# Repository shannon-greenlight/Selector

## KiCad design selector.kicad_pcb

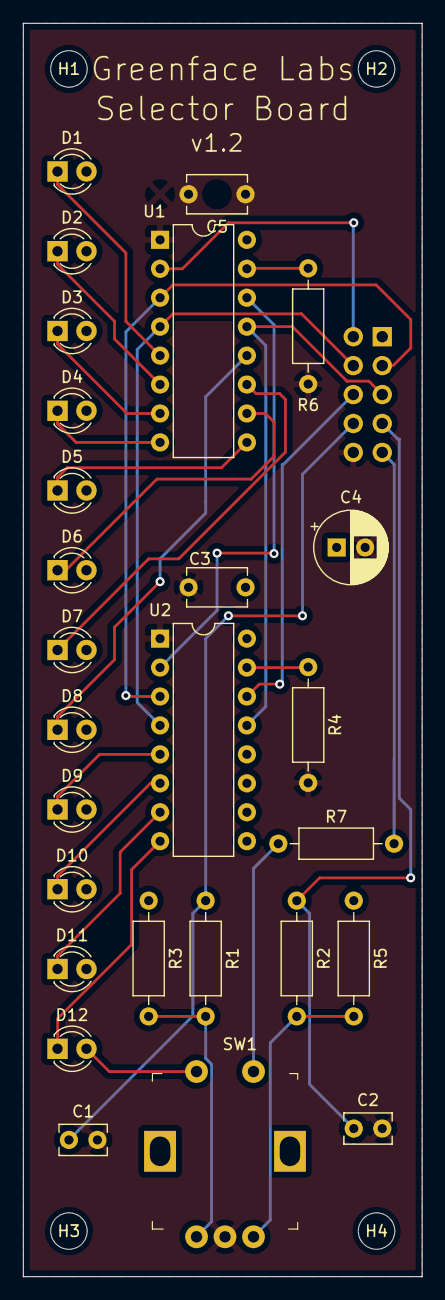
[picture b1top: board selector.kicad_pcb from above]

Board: 2 copper layers, 35.0 x 110.0 mm, 32 parts (1 on the bottom side), 28 nets.

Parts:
C1, C2: .01uF; C_Rect_L4.0mm_W2.5mm_P2.50mm
C3, C5: .1uF; C_Disc_D5.1mm_W3.2mm_P5.00mm
C4: 47uF; CP_Radial_D6.3mm_P2.50mm
D1, D2, D3, D4, D5, D6, D7, D8, D9, D10, D11, D12: Red LED; LED_D3.0mm
H1, H2, H3, H4: MountingHole; MountingHole_3.2mm_M3
J1: Conn_02x05_Odd_Even; PinHeader_2x05_P2.54mm_Vertical
R1, R2, R3, R5: 10K; R_Axial_DIN0207_L6.3mm_D2.5mm_P10.16mm_Horizontal
R4, R6: 2.2K; R_Axial_DIN0207_L6.3mm_D2.5mm_P10.16mm_Horizontal
R7: 1K; R_Axial_DIN0207_L6.3mm_D2.5mm_P10.16mm_Horizontal
SW1: PEC11R; Rotary_Encoder_Switched_PEC11R
U1, U2: TLC5916; DIP-16_W7.62mm

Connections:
+5V: C3.1, C4.1, C5.1, D1.2, D2.2, D3.2, D4.2, D5.2, D6.2, D7.2, D8.2, D9.2, D10.2, D11.2, D12.2, J1.1, R3.1, R5.1, SW1.1, U1.16, U2.16
GND: C1.2, C2.2, C3.2, C4.2, C5.2, J1.10, R4.2, R6.2, SW1.C, U1.1, U2.1
unnamed: C1.1, J1.8, R1.1
unnamed: C2.1, J1.7, R2.1
unnamed: D1.1, U1.5
unnamed: D2.1, U1.6
unnamed: D3.1, U1.7
unnamed: D4.1, U1.8
unnamed: D5.1, U1.9
unnamed: D6.1, U1.10
unnamed: D7.1, U1.11
unnamed: D8.1, U1.12
unnamed: D9.1, U2.5
unnamed: D10.1, U2.6
unnamed: D11.1, U2.7
unnamed: D12.1, U2.8
unnamed: J1.2, U1.2
unnamed: J1.3, U1.3, U2.3
unnamed: J1.4, U1.4, U2.4
unnamed: J1.5, U1.13, U2.13
unnamed: J1.6, U2.14
unnamed: J1.9, R7.2
unnamed: R1.2, R3.2, SW1.A
unnamed: R2.2, R5.2, SW1.B
unnamed: R4.1, U2.15
unnamed: R6.1, U1.15
unnamed: R7.1, SW1.2
unnamed: U1.14, U2.2

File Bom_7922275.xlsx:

Manufacturer Part Number | Manufacturer | Digi-Key Part Number | Customer Reference | Reference Designator | Packaging | Part Status | Quantity | Unit Price | Extended Price | Quantity Available | Mfg Std Lead Time | Description | RoHS Status | Lead Free Status | REACH Status
K103M15X7RF53L2 | Vishay BC Components | BC5136-ND | .01uF | C1 C2 | Bulk | Active | 2 | 0.21000 | $0.42 | 16243 | 10 Weeks | CAP CER 10000PF 50V X7R RADIAL | Not Available | Lead free | Not Available
ECE-A1EKA470I | Panasonic Electronic Components | P19582CT-ND | 47uF | C4 | Cut Tape (CT) | Active | 1 | 0.27000 | $0.27 | 81099 | 15 Weeks | CAP ALUM 47UF 20% 25V RADIAL | RoHS Compliant | Lead free | Not Available
SR215C104KAA | AVX Corporation | 478-2472-ND | .1uF | C5 C3 | Bulk | Active | 2 | 0.20000 | $0.40 | 17131 | 11 Weeks | CAP CER 0.1UF 50V X7R RADIAL | Not Available | Lead free | REACH Unaffected
151031SS04000 | Wurth Electronics Inc. | 732-5005-ND | Red LED | D1 D2 D3 D4 D5 D6 D7 D8 D9 D10 D11 D12 | Bulk | Active | 12 | 0.17000 | $2.04 | 1875 | 11 Weeks | LED RED DIFFUSED 3MM ROUND T/H | ROHS3 Compliant | Lead free | REACH Unaffected
67997-210HLF | Amphenol ICC (FCI) | 609-3236-ND | Conn_02x05_Odd_Even | J1 | Bag | Active | 1 | 0.52000 | $0.52 | 0 | 7 Weeks | CONN HEADER VERT 10POS 2.54MM | RoHS Compliant | Lead free | Not Available
CF14JT10K0 | Stackpole Electronics Inc | CF14JT10K0CT-ND | 10K | R3 R5 R1 R2 | Cut Tape (CT) | Active | 4 | 0.10000 | $0.40 | 866174 | 15 Weeks | RES 10K OHM 1/4W 5% AXIAL | ROHS3 Compliant | Lead free | REACH Unaffected
CF14JT2K20 | Stackpole Electronics Inc | CF14JT2K20CT-ND | 2K | R4 R6 | Cut Tape (CT) | Active | 2 | 0.10000 | $0.20 | 169324 | 15 Weeks | RES 2.2K OHM 1/4W 5% AXIAL | ROHS3 Compliant | Lead free | REACH Unaffected
PEC11R-4315F-S0012 | Bourns Inc. | PEC11R-4315F-S0012-ND | PEC11R | SW1 | Tray | Active | 1 | 1.91000 | $1.91 | 241 | 18 Weeks | ROTARY ENCODER MECHANICAL 12PPR | ROHS3 Compliant | Lead free | REACH Unaffected
TLC5916IN | Texas Instruments | 296-24383-5-ND | TLC5916 | U1 U2 | Tube | Active | 2 | 1.37000 | $2.74 | 25183 | 6 Weeks | IC LED DRIVER LINEAR 120MA 16DIP | ROHS3 Compliant | Lead free | REACH Unaffected
D89110-0131HK-3365/10-D-3 | 3M | 3M156030-MC10G-3M156030-3-ND | Cable | CB1 | Bulk | Active | 1 | 1.59000 | $1.59 | 467 | Not Available | CABLE 10POS SOCKET TO SOCKET 3" | RoHS Compliant | Lead free | Not Available
971070155 | Wurth Electronics Inc. | 732-13045-ND |  |  | Bag | Active | 4 | 0.89000 | $3.56 | 916 | 8 Weeks | PLASTIC SPACER STUD METRIC THREA | ROHS3 Compliant | Lead free | Not Available
4687 | Keystone Electronics | 36-4687-ND |  |  | Bulk | Active | 4 | 0.15000 | $0.60 | 9498 | 6 Weeks | HEX NUT 0.197" NYLON M2.5 | ROHS3 Compliant | Lead free | REACH Unaffected
29331 | Keystone Electronics | 36-29331-ND |  |  | Bulk | Active | 4 | 0.21000 | $0.84 | 3971 | 6 Weeks | MACH SCREW PAN SLOTTED M2.5X0.45 | ROHS3 Compliant | Lead free | REACH Unaffected
LEDM-2-06 | Essentra Components | RPC4260-ND |  |  | Bulk | Active | 12 | 0.31100 | $3.73 | 5773 | 7 Weeks | LED SPACER 3MM T-1 BLACK 6MM | RoHS Compliant | Lead free | REACH Unaffected
OEJNI-50-4-7 | Kilo International | 226-4215-ND | Knob |  | Bulk | Active | 1 | 6.44000 | $6.44 | 110 | 12 Weeks | KNOB KNURLED 0.236" METAL | RoHS Compliant | Lead free | REACH Unaffected
AR 14 HZL-TT | Assmann WSW Components | AE10012-ND |  |  | Tube | Active | 2 | 0.79000 | $1.58 | 5658 | 20 Weeks | CONN IC DIP SOCKET 14POS TIN | ROHS3 Compliant | Lead free | REACH Unaffected
CF14JT1K00 | Stackpole Electronics Inc | CF14JT1K00CT-ND |  | R7 | Cut Tape (CT) | Active | 1 | 0.10000 | $0.10 | 952140 | 15 Weeks | RES 1K OHM 1/4W 5% AXIAL | ROHS3 Compliant | Lead free | REACH Unaffected

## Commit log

2019-06-03 Init checkin
2019-06-03 Adds Front Panel
2019-06-04 Latest changes.
2019-06-04 Gerber files
2019-06-17 Updates BOM
